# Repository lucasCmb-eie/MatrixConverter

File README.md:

# Proyecto De Ingenieria: Matirz de Conmutacion
En este repositorio estaran guardados los codigos tanto de HW (FPGA), como de SW(ARM).

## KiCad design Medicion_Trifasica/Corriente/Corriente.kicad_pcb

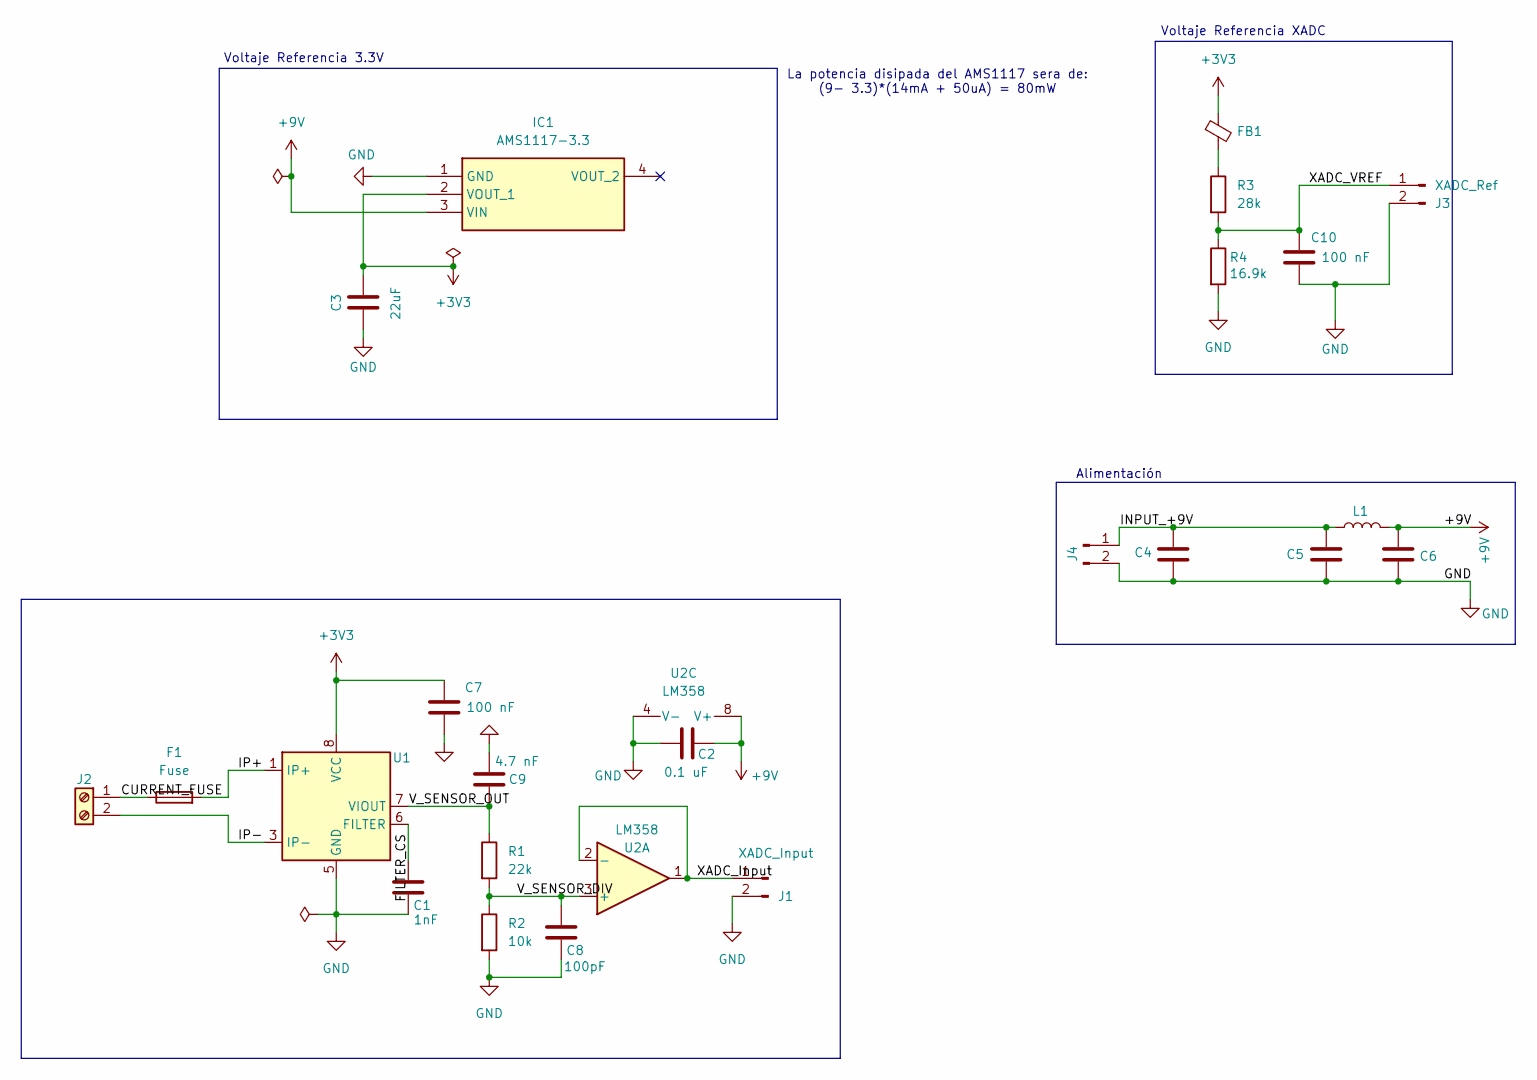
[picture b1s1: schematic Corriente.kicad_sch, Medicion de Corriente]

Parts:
C1: 1nF; C_1206_3216Metric_Pad1.33x1.80mm_HandSolder
C2: 0.1 uF; C_1206_3216Metric_Pad1.33x1.80mm_HandSolder
C3: 22uF; C_1206_3216Metric_Pad1.33x1.80mm_HandSolder
C4: 470 uF; C_1206_3216Metric_Pad1.33x1.80mm_HandSolder
C5, C6, C7, C10: 100 nF; C_1206_3216Metric_Pad1.33x1.80mm_HandSolder
C8: 100pF; C_1206_3216Metric_Pad1.33x1.80mm_HandSolder
C9: 4.7 nF; C_1206_3216Metric_Pad1.33x1.80mm_HandSolder
F1: Fuse; FuseHolder_Blade_ATO_Littelfuse_FLR_178.6165
FB1: FerriteBead_Small; L_0603_1608Metric
IC1: AMS1117-3.3; SOT229P700X180-4N; Manufacturer_Part_Number AMS1117-3.3
J1: XADC_Input; PinHeader_2x01_P2.54mm_Horizontal
J2: Screw_Terminal_01x02; TerminalBlock_bornier-2_P5.08mm
J3: XADC_Ref; PinHeader_2x01_P2.54mm_Horizontal
J4: POWER; PinHeader_1x02_P2.54mm_Vertical
L1: L; L_7.3x7.3_H3.5
R1: 22k; R_0805_2012Metric_Pad1.20x1.40mm_HandSolder
R2: 10k; R_0805_2012Metric_Pad1.20x1.40mm_HandSolder
R3: 28k; R_0805_2012Metric_Pad1.20x1.40mm_HandSolder
R4: 16.9k; R_0805_2012Metric_Pad1.20x1.40mm_HandSolder
U1: ACS725xLCTR-20AB; SOIC-8_3.9x4.9mm_P1.27mm
U2: LM358; SOIC-8_3.9x4.9mm_P1.27mm

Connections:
+3V3: C3.2, C7.1, FB1.1, IC1.2 (VOUT_1), U1.8 (VCC)
+9V: C2.2, C6.2, IC1.3 (VIN), L1.2, U2.8 (V+)
/CURRENT_FUSE: F1.1, J2.1
/FILTER_CS: C1.2, U1.6 (FILTER)
/INPUT_+9V: C4.1, C5.2, J4.1, L1.1
/IP+: F1.2, U1.1 (IP+), U1.2 (IP+)
/IP-: J2.2, U1.3 (IP-), U1.4 (IP-)
/V_SENSOR_DIV: C8.2, R1.2, R2.1, U2.3 (+)
/V_SENSOR_OUT: C9.1, R1.1, U1.7 (VIOUT)
/XADC_Input: J1.1, U2.1, U2.2 (-)
/XADC_VREF: C10.1, J3.1, R3.2, R4.1
GND: C1.1, C2.1, C3.1, C4.2, C5.1, C6.1, C7.2, C8.1, C9.2, C10.2, IC1.1 (GND), J1.2, J3.2, J4.2, R2.2, R4.2, U1.5 (GND), U2.4 (V-)
unnamed: FB1.2, R3.1

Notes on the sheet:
La potencia disipada del AMS1117 sera de: (9- 3.3)*(14mA + 50uA) = 80mW
Alimentación
Voltaje Referencia XADC
Voltaje Referencia 3.3V

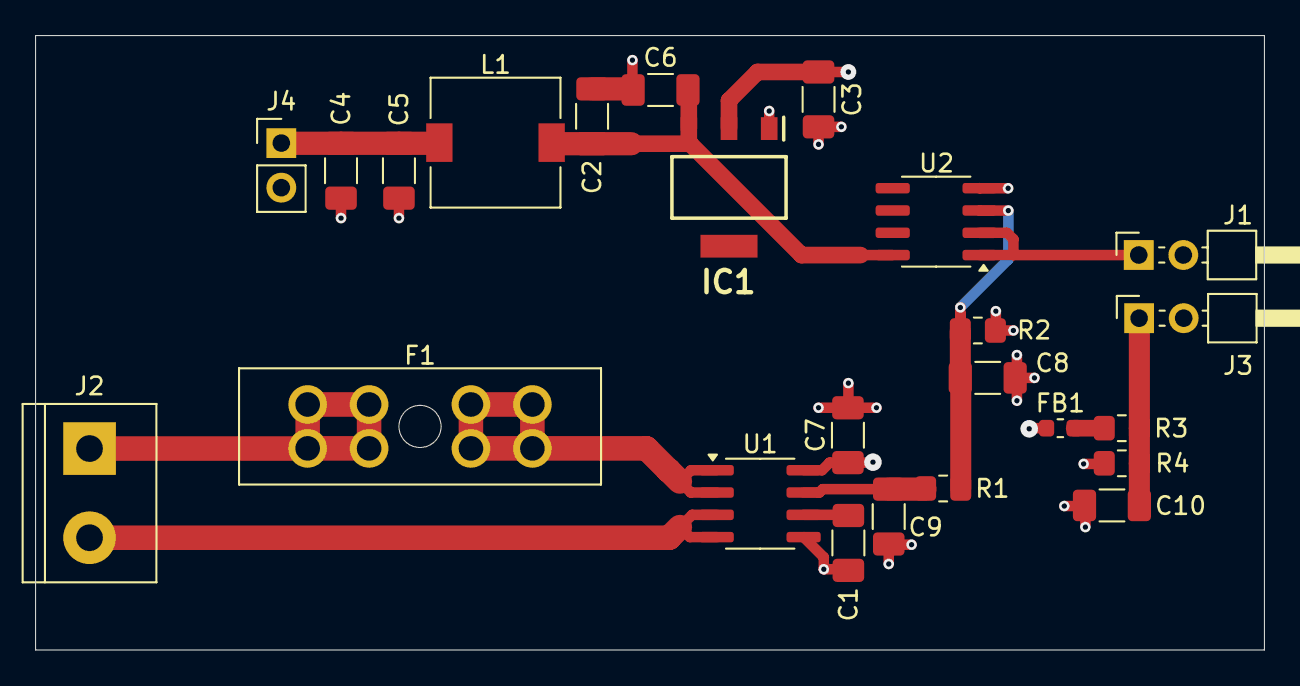
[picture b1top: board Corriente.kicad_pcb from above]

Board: 4 copper layers, 70.0 x 35.0 mm, 24 parts (0 on the bottom side), 13 nets.

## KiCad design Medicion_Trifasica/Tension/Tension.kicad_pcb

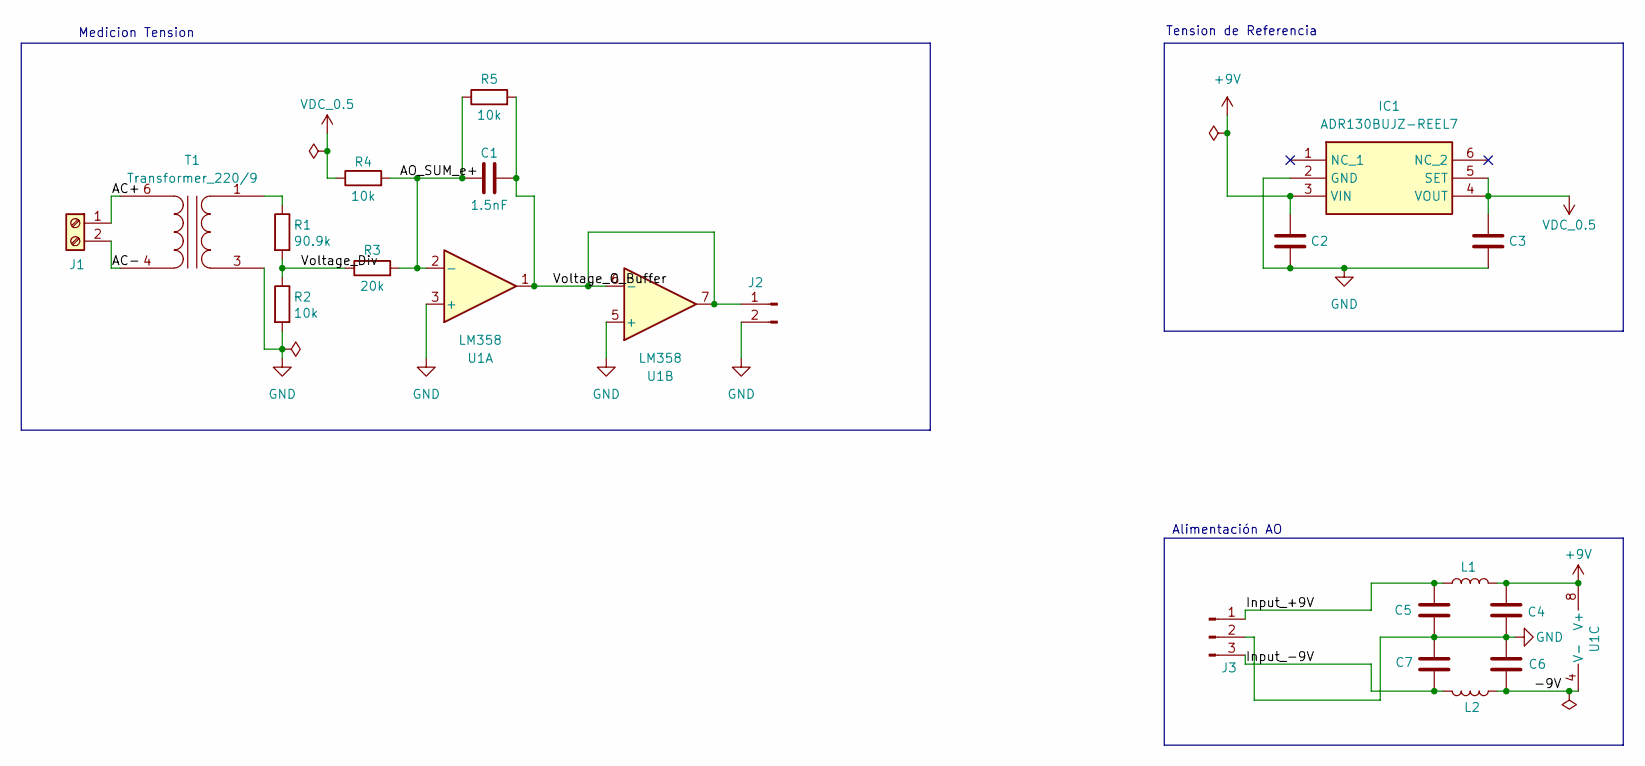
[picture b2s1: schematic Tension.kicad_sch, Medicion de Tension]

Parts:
C1: 1.5nF; C_0402_1005Metric_Pad0.74x0.62mm_HandSolder
C2: 0.1uF; C_0402_1005Metric_Pad0.74x0.62mm_HandSolder
C3: 0.1uf; C_0402_1005Metric_Pad0.74x0.62mm_HandSolder
C4, C5, C6, C7: 100 nF; C_0402_1005Metric_Pad0.74x0.62mm_HandSolder
IC1: ADR130BUJZ-REEL7; SOT95P280X100-6N; Manufacturer_Part_Number ADR130BUJZ-REEL7; Mouser Part Number 584-ADR130BUJZ-R7
J1: Screw_Terminal_01x02; TerminalBlock_bornier-2_P5.08mm
J2: Conn_01x02_Pin; PinHeader_1x02_P2.54mm_Horizontal
J3: Conn_01x03_Pin; PinHeader_1x03_P2.54mm_Vertical
L1, L2: 30 uH; L_7.3x7.3_H3.5
R1: 90.9k; R_0805_2012Metric_Pad1.20x1.40mm_HandSolder
R2, R4, R5: 10k; R_0805_2012Metric_Pad1.20x1.40mm_HandSolder
R3: 20k; R_0805_2012Metric_Pad1.20x1.40mm_HandSolder
T1: Transformer_220/9; Transformer_NF_ETAL_1-1_P1200
U1: LM358; SOIC-8_3.9x4.9mm_P1.27mm

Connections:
+9V: C2.1, C4.2, IC1.3 (VIN), L1.2, U1.8 (V+)
/-9V: C6.2, L2.1, U1.4 (V-)
/AC+: J1.1, T1.6 (AA)
/AC-: J1.2, T1.4 (AB)
/AO_SUM_e+: C1.1, R3.2, R4.2, R5.1, U1.2 (-)
/Input_+9V: C5.2, J3.1, L1.1
/Input_-9V: C7.2, J3.3, L2.2
/Voltage_Div: R1.2, R2.1, R3.1
/Voltage_O_Buffer: C1.2, J2.1, R5.2, U1.1, U1.6 (-), U1.7
GND: C2.2, C3.2, C4.1, C5.1, C6.1, C7.1, IC1.2 (GND), J2.2, J3.2, R2.2, T1.3 (SA), U1.3 (+), U1.5 (+)
unnamed: R1.1, T1.1 (SB)
VDC_0.5: C3.1, IC1.4 (VOUT), IC1.5 (SET), R4.1

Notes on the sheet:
Tension de Referencia
Alimentación AO
Medicion Tension

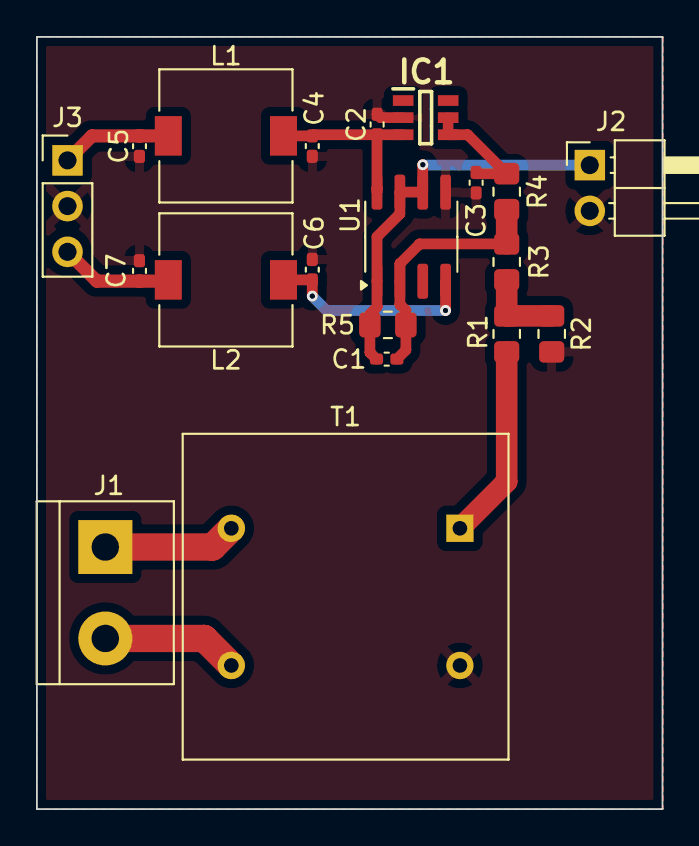
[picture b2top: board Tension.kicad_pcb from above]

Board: 2 copper layers, 34.8 x 42.9 mm, 20 parts (0 on the bottom side), 12 nets.

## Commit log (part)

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2024-12-08 Archivos Base del modulador
    Archivos HDL provistos por Sergio para comenzar el análisis del modulador
2025-01-06 Revision del script de creacion del proyecto
2025-01-06 Nuevos archivos y cambios
    - Se ignora la carpeta proyecto que crea Vivado
    - Se agrego un nuevo hdl con las declaraciones de vector y matiz (VHDL 2008)
2025-01-07 Creacion de bloque TOP y formateo de hdls
    Se creo el bloque Conmutador que va a servir por el momento de TOP.
    Se utilizo el formateador del TerosHDL para mantener un formato de codigo estandar
2025-01-09 Nuevo objetivo
    Los observadores de salida y entrada seran realizados mediante el ARM
2025-01-09 Modulador VHDL 2008
    Este bloque modulador sera implementado con las nuevas caracteristicas que trae el VHDL 2008
2025-01-11 Actualizacion Modulador y creacion de Tb
    Se reviso y borro señales del Modulador que no poseian uso, ademas de hacer una simple documentacion.
    Se creo un TB del mismo bloque tomando en base la que se hizo en la materia Dig4
2025-01-14 Correcion de comentarios
2025-01-15 Correcion del build.tcl
    Se creo un script tcl para la creacion del proyecto cuando se clona degit
2025-01-16 Correciones Modulador y TestBench
    Se eliminaron pines sin uso despues de reunion con Sergio. Y se adecuo el TestBench a estos cambios
2025-01-25 Agregado del IP AXI del Modulador
    Se creo la primera version del bloque AXI del Modulador
2025-01-31 Creacion de un modelo de AXI Modulador
    Se crea una primera version del modulador con conexiones AXI
2025-02-15 Implementacion AXI del Modulador
2025-02-15 Simplifaciones del AXI Stream de las direcciones
2025-03-31 Se agrego un control de Enable al modulador
2025-05-24 Axi Modulador solo tendra entrada de parametros, y saldra las direcciones directamente para usar como coeficientes para realizar un producto
2025-05-25 Se agregaron los bloques del AC Source, con una LUT de una señal senoidal, y un testbecnh que prueba la obtencion de la misma
2025-06-20 Se actualizaron los bloues de AC y la matrix conmutadora. Seagrego el tb del ADSource
2025-06-24 Esquematicos de las mediciones
2025-06-28 Se agrego el circuito de medicion de corriente
2025-06-28 Se agregaron valores a la medicion de tension
2025-07-11 Modificaciones finales a los circuitos de medicion de corriente y tension
2025-08-18 Normalizacion de codigo y creacion de bloque Matriz Conmutadora
2025-08-19 El reset ahora no es negado, y se hizo que las tensiones sean vectores y no matrices ya que era innecesario
2025-09-01 Modelo RL y script de Params
    Se creo el modelo del RL como un IIR, y ademas un script de Jupyter Notebook para hacer el calculo de los coeficientes del filtro
2025-09-05 Se genero una nueva LUT para la senoide con mejor precision y mediante python. Se actualizo el AC_Source con la nueva senoide y el Tb
2025-09-09 Se corrigio el pkg del seno que habia un valor max que estaba mal formado. Se acomodaron las señales de la matrixConmut para ser compatible con el Q8.24
2025-09-10 Correcion en RL
2025-09-11 Se uso el componente existente RL para crear la carga trifasica, y se agrego un vector de fixed para utilizar en el algoritmo
2025-09-11 Agregado de testbench para RL
2025-09-11 Se actualizo el testbench de RL
2025-09-22 Bloque y Tb de la Transformada de Clark
2025-09-22 Limpieza
2025-09-22 Creacion del componente DienteSierra, su Tb y actualizar el build
2025-09-23 Creacion del generador de diente de sierra
2025-09-23 Se acorto la frecuencia de entrada del diente de sierra a 1MHz para simulacion mas rapida
2025-09-25 Se crearon wrappers de cada componente para poder usarlos en el Block Design
2025-09-25 Se agregaron los wrappers al build.tck, y ademas el script para crear el diagrama de bloques
2025-10-28 Bloque Generador Diente de Sierra
    Este bloque genera un diente de sierra de valores 0 a 2pi respecto a la senoide de la T Clark para el alpha i del Modulador
2025-11-01 IPs Sin Axi
2025-11-01 Adaptacion de bloques a un clk de 100MHz
2025-11-03 Adaptacion a 100MHz de clk
2025-11-08 Se elimino lo mas posible el uso de Declaraciones.vhd y los bloques ip creados que estaban mal
2025-11-08 Se creo un componente de RL monofasico y se implementa por cada fase en el wrapper para mayor segmentacion de la carga trifasica
2025-11-09 Regeneracion de los IP sin axi de cada bloque y correcion del tb_RL que generaba problemas al simular
2025-11-15 Se crearon los esquematicos de los circuitos, y sus footprints
2025-11-19 PCB de la medicion de corriente
2025-11-19 Mejoras PCB medicion tension
2025-11-29 Se volvio para atras el cambio de la precision fraccionaria
2025-12-06 Correciones PCBs
2025-12-09 Modelado y pruebas en MatLab del sistema, para 50Hz y 100Hz a la salida
2025-12-09 Optimización de la matriz conmutadora
2025-12-14 Mejora en la organizacion de los circuitos con netclases y colores
2025-12-15 Testbench del funcionamiento del SVM sin carga
2025-12-16 Correcion del modulador, y la simulacion en MatLab
2025-12-18 Reconexión de la PCB, y terminación de conexiones
2025-12-24 Mejoras y trabajos realizadps
2026-01-06 Limpieza y actualización del build del proyecto
2026-01-20 Correciones de VHDL, y creacion del proyecto en Vitis
2026-01-20 Ignoro todo lo que genera el Vitis
2026-02-14 Limpieza, se deja todo lo del PL
2026-02-16 Se creo el bloque CORDIC_atan2 para reemplazar al diente de sierraGen
2026-04-21 Informe tecnico
